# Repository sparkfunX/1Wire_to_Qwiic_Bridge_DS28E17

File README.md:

# Qwiic_1Wire_to_I2C_Bridge_DS28E17
A 1Wire-to- I2C bridge for extending the length of wired I2C networks. For Qwiic Ecosystem.

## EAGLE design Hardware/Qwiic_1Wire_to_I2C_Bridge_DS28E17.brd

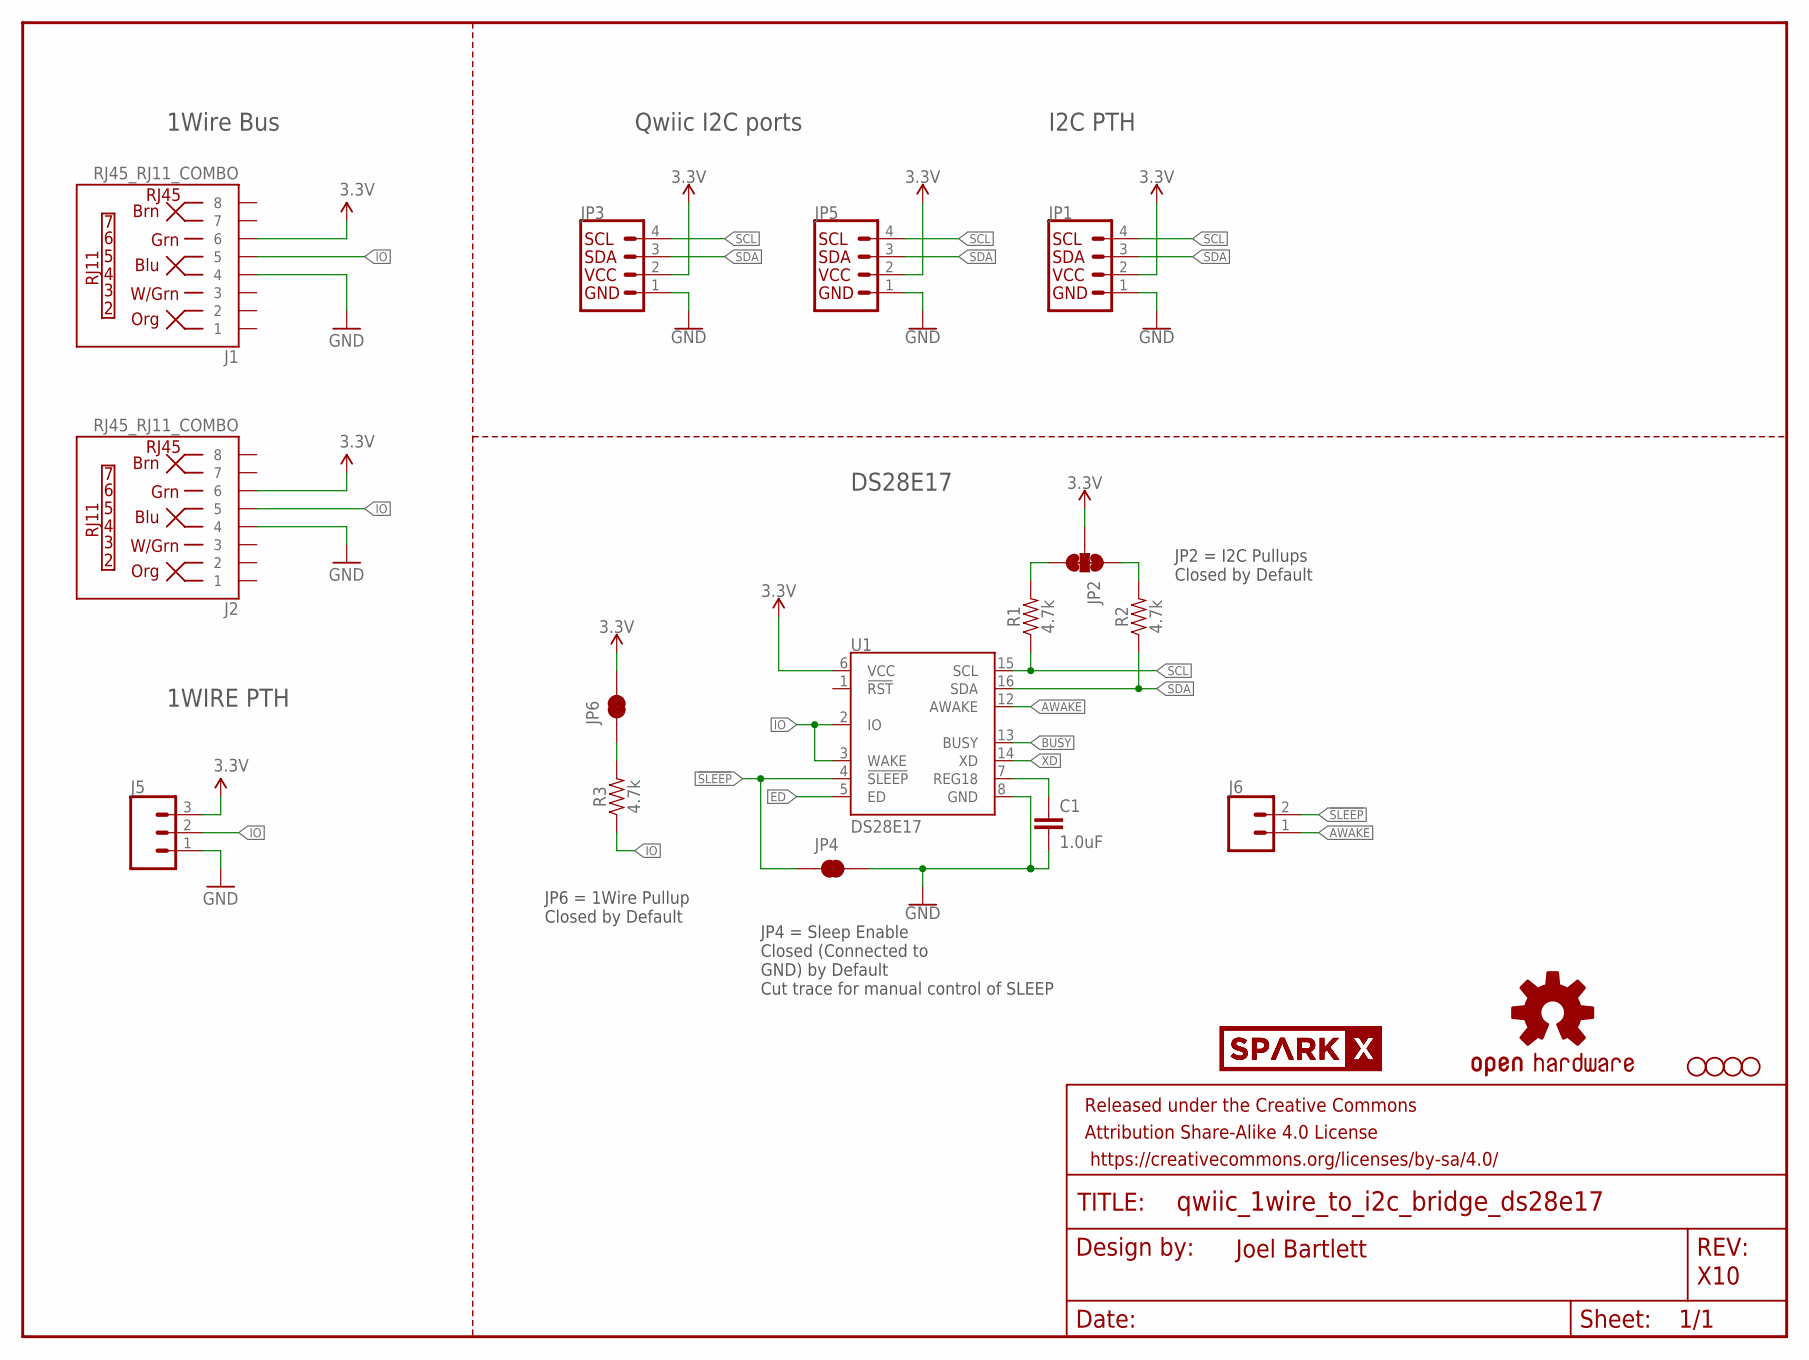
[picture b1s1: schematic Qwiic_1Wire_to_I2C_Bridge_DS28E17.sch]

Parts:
C1: 1.0uF; 0603
FRAME1: FRAME-LETTER; CREATIVE_COMMONS
H1, H2, H3, H4: STAND-OFF
J1, J2: RJ45_RJ11_COMBO
J5: CONN_03; 1X03
J6: CONN_02; 1X02
JP1: I2C_STANDARDSILK; 1X04
JP2: JUMPER-SMT_3_2-NC_TRACE_SILK; SMT-JUMPER_3_2-NC_TRACE_SILK
JP3, JP5: I2C_STANDARDJS-1MM; 1X04_1MM_RA
JP4, JP6: JUMPER-SMT_2_NC_TRACE_SILK; SMT-JUMPER_2_NC_TRACE_SILK
LOGO1: OSHW-LOGOM; OSHW-LOGO-M
R1, R2, R3: 4.7k; 0603
U1: DS28E17; TQFN-16
U$2, U$3: SPARKX-LOGO5; SPARKX-LARGE

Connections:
3.3V: J1.6, J2.6, J5.3, JP1.2 (VCC), JP2.2, JP3.2 (VCC), JP5.2 (VCC), JP6.2, U1.6 (VCC)
!SLEEP: J6.2, JP4.1, U1.4 (!SLEEP)
AWAKE: J6.1, U1.12 (AWAKE)
BUSY: U1.13 (BUSY)
ED: U1.5 (ED)
GND: C1.2, J1.4, J2.4, J5.1, JP1.1 (GND), JP3.1 (GND), JP4.2, JP5.1 (GND), U1.8 (GND)
IO: J1.5, J2.5, J5.2, R3.1, U1.2 (IO), U1.3 (WAKE)
unnamed: C1.1, U1.7 (REG18)
unnamed: JP6.1, R3.2
unnamed: JP2.1, R2.2
unnamed: JP2.3, R1.2
SCL: JP1.4 (SCL), JP3.4 (SCL), JP5.4 (SCL), R1.1, U1.15 (SCL)
SDA: JP1.3 (SDA), JP3.3 (SDA), JP5.3 (SDA), R2.1, U1.16 (SDA)
XD: U1.14 (XD)

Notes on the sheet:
1Wire Bus
Joel Bartlett
Qwiic I2C ports
X10
I2C PTH
DS28E17
1WIRE PTH
JP2 = I2C Pullups Closed by Default
JP6 = 1Wire Pullup Closed by Default
JP4 = Sleep Enable Closed (Connected to GND) by Default Cut trace for manual control of SLEEP

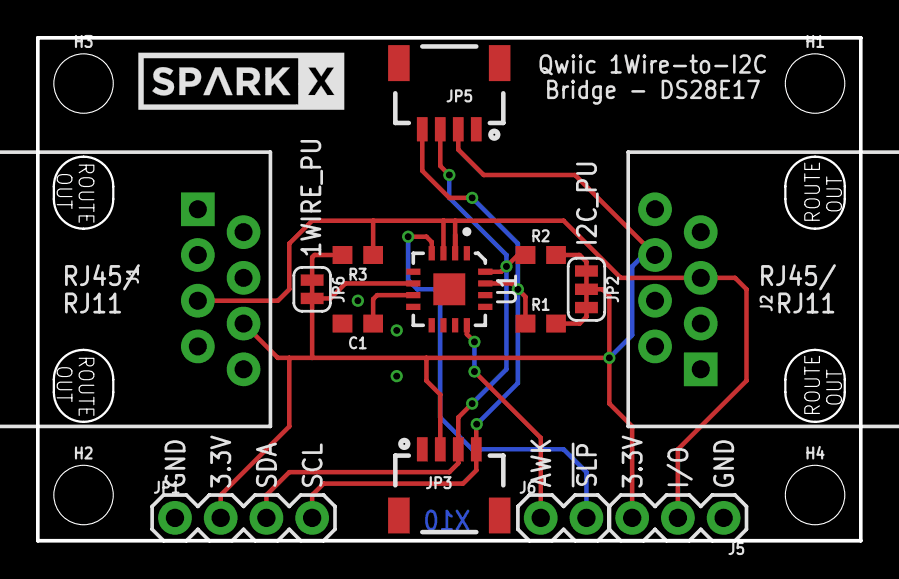
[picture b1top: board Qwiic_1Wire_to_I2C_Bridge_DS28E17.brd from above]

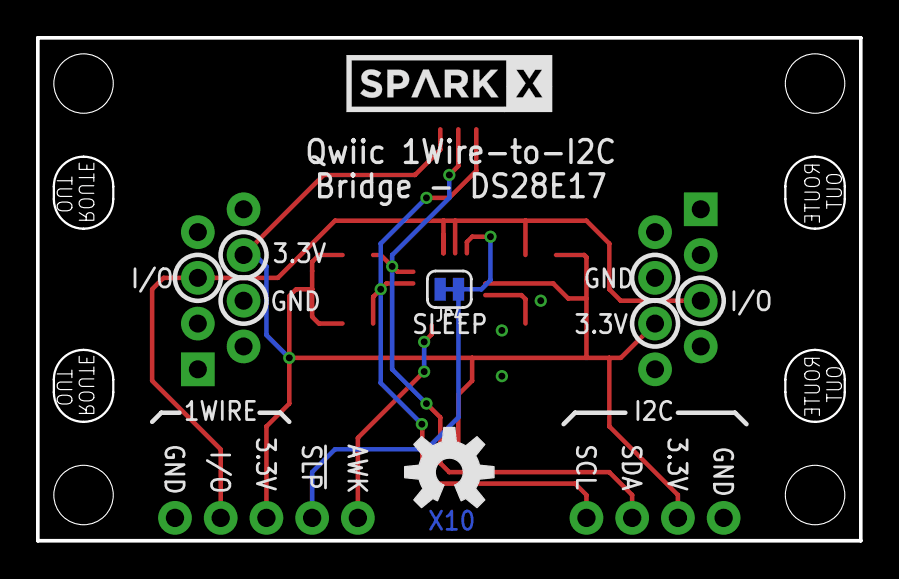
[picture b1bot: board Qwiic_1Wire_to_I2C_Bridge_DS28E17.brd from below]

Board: 2 copper layers, 45.7 x 27.9 mm, 23 parts (3 on the bottom side), 11 nets.

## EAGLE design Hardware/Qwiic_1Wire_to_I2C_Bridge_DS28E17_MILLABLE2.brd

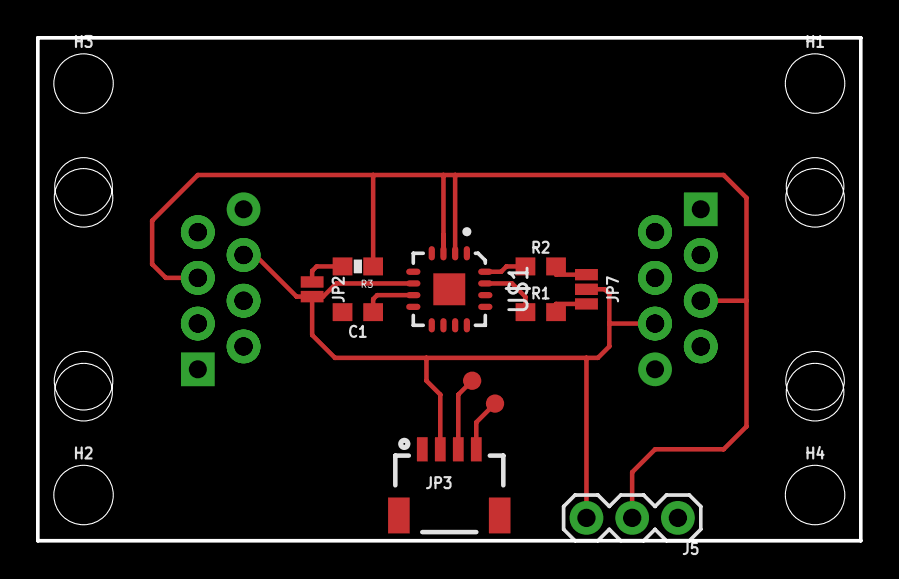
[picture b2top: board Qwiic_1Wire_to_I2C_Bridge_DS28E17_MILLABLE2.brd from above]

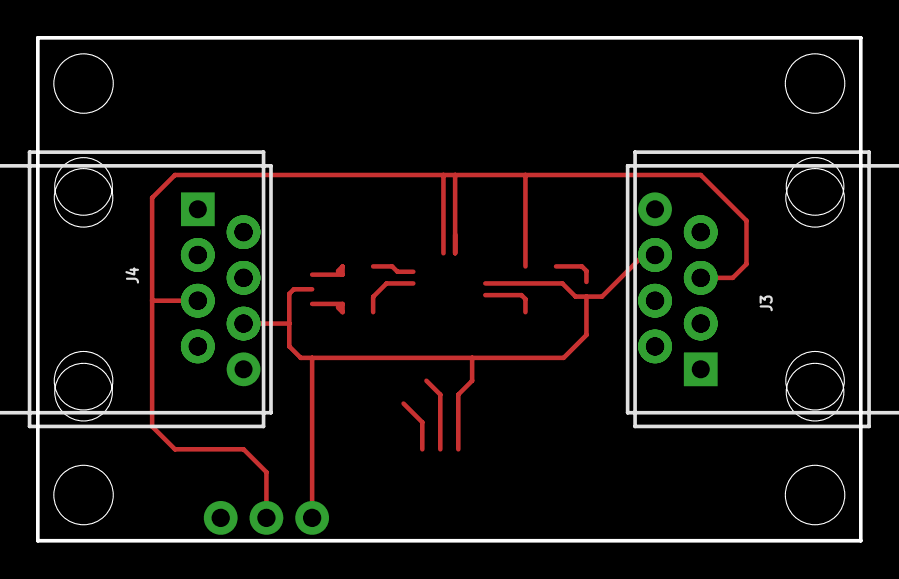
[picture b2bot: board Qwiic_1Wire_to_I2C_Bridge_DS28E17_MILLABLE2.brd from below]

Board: 2 copper layers, 45.7 x 27.9 mm, 20 parts (4 on the bottom side), 11 nets.

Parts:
C1: 1.0uF; 0603
FRAME1: FRAME-LETTER; CREATIVE_COMMONS
H1, H2, H3, H4: STAND-OFF
J1, J2: RJ45; RJ45-8
J3, J4: RJ11; RJ11-6
J5: 1X03
JP2: SMT-JUMPER_2_NO_NO-SILK
JP3: 1X04_1MM_RA
JP7: SMT-JUMPER_3_NO_NO-SILK
R1, R2: 4.7k; 0603
R3: 4.7K; 0603-RES
TP1, TP2: TEST-POINT3X4; PAD.03X.04
U$1: DS28E17; TQFN-16

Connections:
3.3V: J1.6, J2.6, J3.5, J4.5, J5.3, JP2.2, JP3.2, JP7.2, U$1.6
GND: C1.2, J1.4, J2.4, J3.3, J4.3, J5.1, JP3.1, U$1.4, U$1.8
IO: J1.5, J2.5, J3.4, J4.4, J5.2, R3.1, U$1.2, U$1.3
unnamed: C1.1, U$1.7
unnamed: JP2.1, R3.2
unnamed: JP7.1, R2.2
unnamed: JP7.3, R1.2
unnamed: JP3.4, TP1.P$1
unnamed: JP3.3, TP2.P$1
SCL: R1.1, U$1.15
SDA: R2.1, U$1.16

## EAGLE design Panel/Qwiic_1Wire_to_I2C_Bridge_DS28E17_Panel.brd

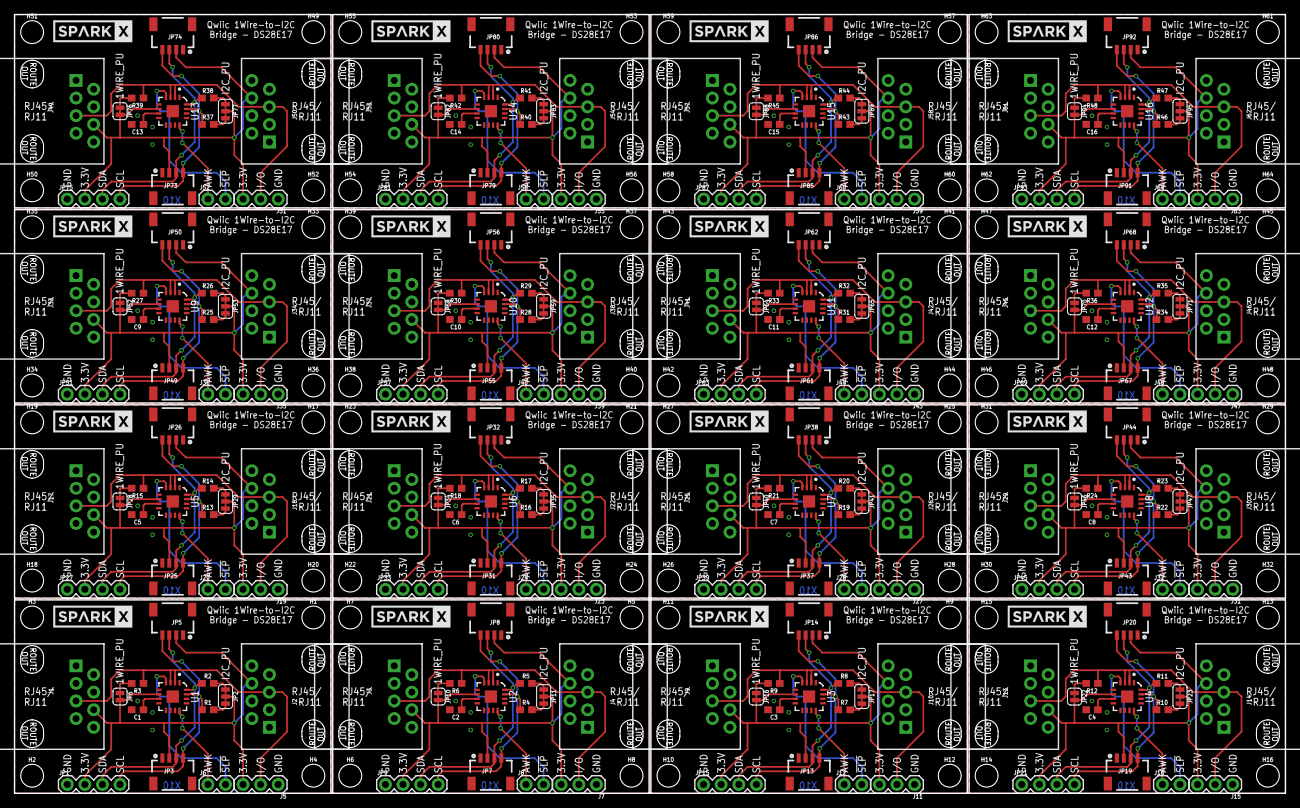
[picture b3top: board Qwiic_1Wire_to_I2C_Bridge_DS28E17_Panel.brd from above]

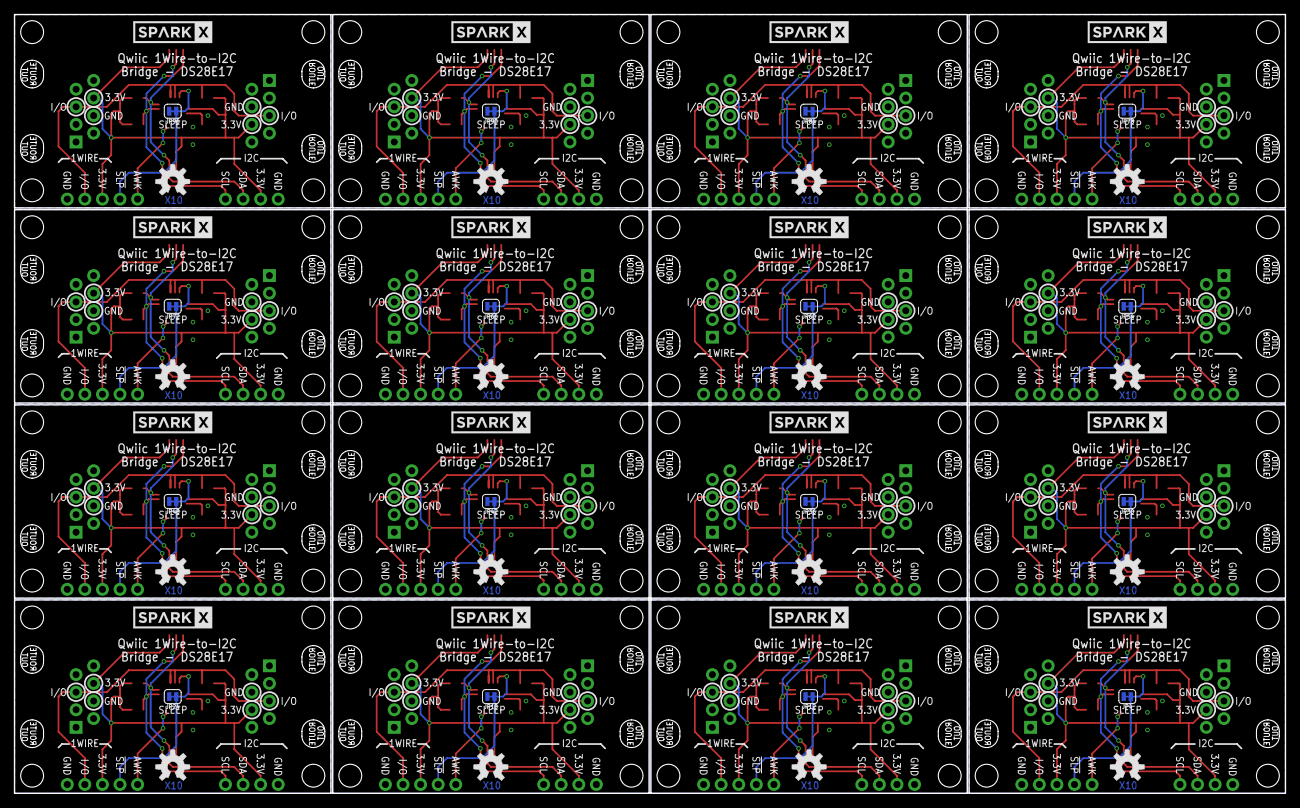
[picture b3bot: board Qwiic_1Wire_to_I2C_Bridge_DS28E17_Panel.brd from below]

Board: 2 copper layers, 183.6 x 112.5 mm, 353 parts (48 on the bottom side), 176 nets.

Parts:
C1, C2, C3, C4, C5, C6, C7, C8, C9, C10, C11, C12, C13, C14, C15, C16: 1.0uF; 0603
FRAME1: FRAME-LETTER; CREATIVE_COMMONS
H1, H2, H3, H4, H5, H6, H7, H8, H9, H10, H11, H12, H13, H14, H15, H16, H17, H18, H19, H20, H21, H22, H23, H24, H25, H26, H27, H28, H29, H30, H31, H32, H33, H34, H35, H36, H37, H38, H39, H40, H41, H42, H43, H44, H45, H46, H47, H48, H49, H50, H51, H52, H53, H54, H55, H56, H57, H58, H59, H60, H61, H62, H63, H64: STAND-OFF
J1, J2, J3, J4, J9, J10, J13, J14, J17, J18, J21, J22, J25, J26, J29, J30, J33, J34, J37, J38, J41, J42, J45, J46, J49, J50, J53, J54, J57, J58, J61, J62: RJ45_RJ11_COMBO
J5, J7, J11, J15, J19, J23, J27, J31, J35, J39, J43, J47, J51, J55, J59, J63: 1X03
J6, J8, J12, J16, J20, J24, J28, J32, J36, J40, J44, J48, J52, J56, J60, J64: 1X02
JP1, JP9, JP15, JP21, JP27, JP33, JP39, JP45, JP51, JP57, JP63, JP69, JP75, JP81, JP87, JP93: 1X04
JP2, JP11, JP17, JP23, JP29, JP35, JP41, JP47, JP53, JP59, JP65, JP71, JP77, JP83, JP89, JP95: SMT-JUMPER_3_2-NC_TRACE_SILK
JP3, JP5, JP7, JP8, JP13, JP14, JP19, JP20, JP25, JP26, JP31, JP32, JP37, JP38, JP43, JP44, JP49, JP50, JP55, JP56, JP61, JP62, JP67, JP68, JP73, JP74, JP79, JP80, JP85, JP86, JP91, JP92: 1X04_1MM_RA
JP4, JP6, JP10, JP12, JP16, JP18, JP22, JP24, JP28, JP30, JP34, JP36, JP40, JP42, JP46, JP48, JP52, JP54, JP58, JP60, JP64, JP66, JP70, JP72, JP76, JP78, JP82, JP84, JP88, JP90, JP94, JP96: SMT-JUMPER_2_NC_TRACE_SILK
LOGO1, LOGO2, LOGO3, LOGO4, LOGO5, LOGO6, LOGO7, LOGO8, LOGO9, LOGO10, LOGO11, LOGO12, LOGO13, LOGO14, LOGO15, LOGO16: OSHW-LOGOM; OSHW-LOGO-M
R1, R2, R3, R4, R5, R6, R7, R8, R9, R10, R11, R12, R13, R14, R15, R16, R17, R18, R19, R20, R21, R22, R23, R24, R25, R26, R27, R28, R29, R30, R31, R32, R33, R34, R35, R36, R37, R38, R39, R40, R41, R42, R43, R44, R45, R46, R47, R48: 4.7k; 0603
U1, U2, U3, U4, U5, U6, U7, U8, U9, U10, U11, U12, U13, U14, U15, U16: DS28E17; TQFN-16
U$1, U$2, U$3, U$4, U$5, U$6, U$7, U$8, U$9, U$10, U$11, U$12, U$13, U$14, U$15, U$16, U$17, U$18, U$19, U$20, U$21, U$22, U$23, U$24, U$25, U$26, U$27, U$28, U$29, U$30, U$31, U$32: SPARKX-LOGO5; SPARKX-LARGE

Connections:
3.3V: J1.6, J2.6, J5.3, JP1.2, JP2.2, JP3.2, JP5.2, JP6.2, U1.6
3.3V1: J3.6, J4.6, J7.3, JP7.2, JP8.2, JP9.2, JP10.2, JP11.2, U2.6
3.3V2: J9.6, J10.6, J11.3, JP13.2, JP14.2, JP15.2, JP16.2, JP17.2, U3.6
3.3V3: J13.6, J14.6, J15.3, JP19.2, JP20.2, JP21.2, JP22.2, JP23.2, U4.6
3.3V4: J17.6, J18.6, J19.3, JP25.2, JP26.2, JP27.2, JP28.2, JP29.2, U5.6
3.3V5: J21.6, J22.6, J23.3, JP31.2, JP32.2, JP33.2, JP34.2, JP35.2, U6.6
3.3V6: J25.6, J26.6, J27.3, JP37.2, JP38.2, JP39.2, JP40.2, JP41.2, U7.6
3.3V7: J29.6, J30.6, J31.3, JP43.2, JP44.2, JP45.2, JP46.2, JP47.2, U8.6
3.3V8: J33.6, J34.6, J35.3, JP49.2, JP50.2, JP51.2, JP52.2, JP53.2, U9.6
3.3V9: J37.6, J38.6, J39.3, JP55.2, JP56.2, JP57.2, JP58.2, JP59.2, U10.6
3.3V10: J41.6, J42.6, J43.3, JP61.2, JP62.2, JP63.2, JP64.2, JP65.2, U11.6
3.3V11: J45.6, J46.6, J47.3, JP67.2, JP68.2, JP69.2, JP70.2, JP71.2, U12.6
3.3V12: J49.6, J50.6, J51.3, JP73.2, JP74.2, JP75.2, JP76.2, JP77.2, U13.6
3.3V13: J53.6, J54.6, J55.3, JP79.2, JP80.2, JP81.2, JP82.2, JP83.2, U14.6
3.3V14: J57.6, J58.6, J59.3, JP85.2, JP86.2, JP87.2, JP88.2, JP89.2, U15.6
3.3V15: J61.6, J62.6, J63.3, JP91.2, JP92.2, JP93.2, JP94.2, JP95.2, U16.6
!SLEEP: J6.2, JP4.1, U1.4
!SLEEP1: J8.2, JP12.1, U2.4
!SLEEP2: J12.2, JP18.1, U3.4
!SLEEP3: J16.2, JP24.1, U4.4
!SLEEP4: J20.2, JP30.1, U5.4
!SLEEP5: J24.2, JP36.1, U6.4
!SLEEP6: J28.2, JP42.1, U7.4
!SLEEP7: J32.2, JP48.1, U8.4
!SLEEP8: J36.2, JP54.1, U9.4
!SLEEP9: J40.2, JP60.1, U10.4
!SLEEP10: J44.2, JP66.1, U11.4
!SLEEP11: J48.2, JP72.1, U12.4
!SLEEP12: J52.2, JP78.1, U13.4
!SLEEP13: J56.2, JP84.1, U14.4
!SLEEP14: J60.2, JP90.1, U15.4
!SLEEP15: J64.2, JP96.1, U16.4
AWAKE: J6.1, U1.12
AWAKE1: J8.1, U2.12
AWAKE2: J12.1, U3.12
AWAKE3: J16.1, U4.12
AWAKE4: J20.1, U5.12
AWAKE5: J24.1, U6.12
AWAKE6: J28.1, U7.12
AWAKE7: J32.1, U8.12
AWAKE8: J36.1, U9.12
AWAKE9: J40.1, U10.12
AWAKE10: J44.1, U11.12
AWAKE11: J48.1, U12.12
AWAKE12: J52.1, U13.12
AWAKE13: J56.1, U14.12
AWAKE14: J60.1, U15.12
AWAKE15: J64.1, U16.12
GND: C1.2, J1.4, J2.4, J5.1, JP1.1, JP3.1, JP4.2, JP5.1, U1.8
GND1: C2.2, J3.4, J4.4, J7.1, JP7.1, JP8.1, JP9.1, JP12.2, U2.8
GND2: C3.2, J9.4, J10.4, J11.1, JP13.1, JP14.1, JP15.1, JP18.2, U3.8
GND3: C4.2, J13.4, J14.4, J15.1, JP19.1, JP20.1, JP21.1, JP24.2, U4.8
GND4: C5.2, J17.4, J18.4, J19.1, JP25.1, JP26.1, JP27.1, JP30.2, U5.8
GND5: C6.2, J21.4, J22.4, J23.1, JP31.1, JP32.1, JP33.1, JP36.2, U6.8
GND6: C7.2, J25.4, J26.4, J27.1, JP37.1, JP38.1, JP39.1, JP42.2, U7.8
GND7: C8.2, J29.4, J30.4, J31.1, JP43.1, JP44.1, JP45.1, JP48.2, U8.8
GND8: C9.2, J33.4, J34.4, J35.1, JP49.1, JP50.1, JP51.1, JP54.2, U9.8
GND9: C10.2, J37.4, J38.4, J39.1, JP55.1, JP56.1, JP57.1, JP60.2, U10.8
GND10: C11.2, J41.4, J42.4, J43.1, JP61.1, JP62.1, JP63.1, JP66.2, U11.8
GND11: C12.2, J45.4, J46.4, J47.1, JP67.1, JP68.1, JP69.1, JP72.2, U12.8
GND12: C13.2, J49.4, J50.4, J51.1, JP73.1, JP74.1, JP75.1, JP78.2, U13.8
GND13: C14.2, J53.4, J54.4, J55.1, JP79.1, JP80.1, JP81.1, JP84.2, U14.8
GND14: C15.2, J57.4, J58.4, J59.1, JP85.1, JP86.1, JP87.1, JP90.2, U15.8
GND15: C16.2, J61.4, J62.4, J63.1, JP91.1, JP92.1, JP93.1, JP96.2, U16.8
IO: J1.5, J2.5, J5.2, R3.1, U1.2, U1.3
IO1: J3.5, J4.5, J7.2, R6.1, U2.2, U2.3
IO2: J9.5, J10.5, J11.2, R9.1, U3.2, U3.3
IO3: J13.5, J14.5, J15.2, R12.1, U4.2, U4.3
IO4: J17.5, J18.5, J19.2, R15.1, U5.2, U5.3
IO5: J21.5, J22.5, J23.2, R18.1, U6.2, U6.3
IO6: J25.5, J26.5, J27.2, R21.1, U7.2, U7.3
IO7: J29.5, J30.5, J31.2, R24.1, U8.2, U8.3
IO8: J33.5, J34.5, J35.2, R27.1, U9.2, U9.3
IO9: J37.5, J38.5, J39.2, R30.1, U10.2, U10.3
IO10: J41.5, J42.5, J43.2, R33.1, U11.2, U11.3
IO11: J45.5, J46.5, J47.2, R36.1, U12.2, U12.3
IO12: J49.5, J50.5, J51.2, R39.1, U13.2, U13.3
IO13: J53.5, J54.5, J55.2, R42.1, U14.2, U14.3
IO14: J57.5, J58.5, J59.2, R45.1, U15.2, U15.3
IO15: J61.5, J62.5, J63.2, R48.1, U16.2, U16.3
unnamed: C1.1, U1.7
unnamed: JP6.1, R3.2
unnamed: JP2.1, R2.2
unnamed: JP2.3, R1.2
unnamed: C2.1, U2.7
unnamed: JP10.1, R6.2
unnamed: JP11.1, R5.2
unnamed: JP11.3, R4.2
unnamed: C3.1, U3.7
unnamed: JP16.1, R9.2
unnamed: JP17.1, R8.2
unnamed: JP17.3, R7.2
unnamed: C4.1, U4.7
unnamed: JP22.1, R12.2
unnamed: JP23.1, R11.2
unnamed: JP23.3, R10.2
unnamed: C5.1, U5.7
unnamed: JP28.1, R15.2
unnamed: JP29.1, R14.2
unnamed: JP29.3, R13.2
unnamed: C6.1, U6.7
unnamed: JP34.1, R18.2
unnamed: JP35.1, R17.2
unnamed: JP35.3, R16.2
unnamed: C7.1, U7.7
unnamed: JP40.1, R21.2
unnamed: JP41.1, R20.2
unnamed: JP41.3, R19.2
unnamed: C8.1, U8.7
unnamed: JP46.1, R24.2
unnamed: JP47.1, R23.2
unnamed: JP47.3, R22.2
unnamed: C9.1, U9.7
unnamed: JP52.1, R27.2
unnamed: JP53.1, R26.2
unnamed: JP53.3, R25.2
unnamed: C10.1, U10.7
unnamed: JP58.1, R30.2
unnamed: JP59.1, R29.2
unnamed: JP59.3, R28.2
unnamed: C11.1, U11.7
unnamed: JP64.1, R33.2
unnamed: JP65.1, R32.2
unnamed: JP65.3, R31.2
unnamed: C12.1, U12.7
unnamed: JP70.1, R36.2
unnamed: JP71.1, R35.2
unnamed: JP71.3, R34.2
unnamed: C13.1, U13.7
unnamed: JP76.1, R39.2
unnamed: JP77.1, R38.2
unnamed: JP77.3, R37.2
unnamed: C14.1, U14.7
unnamed: JP82.1, R42.2
unnamed: JP83.1, R41.2
unnamed: JP83.3, R40.2
unnamed: C15.1, U15.7
unnamed: JP88.1, R45.2
unnamed: JP89.1, R44.2
unnamed: JP89.3, R43.2
unnamed: C16.1, U16.7
unnamed: JP94.1, R48.2
unnamed: JP95.1, R47.2
unnamed: JP95.3, R46.2
SCL: JP1.4, JP3.4, JP5.4, R1.1, U1.15
SCL1: JP7.4, JP8.4, JP9.4, R4.1, U2.15
SCL2: JP13.4, JP14.4, JP15.4, R7.1, U3.15
SCL3: JP19.4, JP20.4, JP21.4, R10.1, U4.15
SCL4: JP25.4, JP26.4, JP27.4, R13.1, U5.15
SCL5: JP31.4, JP32.4, JP33.4, R16.1, U6.15
SCL6: JP37.4, JP38.4, JP39.4, R19.1, U7.15
SCL7: JP43.4, JP44.4, JP45.4, R22.1, U8.15
SCL8: JP49.4, JP50.4, JP51.4, R25.1, U9.15
SCL9: JP55.4, JP56.4, JP57.4, R28.1, U10.15
SCL10: JP61.4, JP62.4, JP63.4, R31.1, U11.15
SCL11: JP67.4, JP68.4, JP69.4, R34.1, U12.15
SCL12: JP73.4, JP74.4, JP75.4, R37.1, U13.15
SCL13: JP79.4, JP80.4, JP81.4, R40.1, U14.15
SCL14: JP85.4, JP86.4, JP87.4, R43.1, U15.15
SCL15: JP91.4, JP92.4, JP93.4, R46.1, U16.15
SDA: JP1.3, JP3.3, JP5.3, R2.1, U1.16
SDA1: JP7.3, JP8.3, JP9.3, R5.1, U2.16
SDA2: JP13.3, JP14.3, JP15.3, R8.1, U3.16
SDA3: JP19.3, JP20.3, JP21.3, R11.1, U4.16
SDA4: JP25.3, JP26.3, JP27.3, R14.1, U5.16
SDA5: JP31.3, JP32.3, JP33.3, R17.1, U6.16
SDA6: JP37.3, JP38.3, JP39.3, R20.1, U7.16
SDA7: JP43.3, JP44.3, JP45.3, R23.1, U8.16
SDA8: JP49.3, JP50.3, JP51.3, R26.1, U9.16
SDA9: JP55.3, JP56.3, JP57.3, R29.1, U10.16
SDA10: JP61.3, JP62.3, JP63.3, R32.1, U11.16
SDA11: JP67.3, JP68.3, JP69.3, R35.1, U12.16
SDA12: JP73.3, JP74.3, JP75.3, R38.1, U13.16
SDA13: JP79.3, JP80.3, JP81.3, R41.1, U14.16
SDA14: JP85.3, JP86.3, JP87.3, R44.1, U15.16
SDA15: JP91.3, JP92.3, JP93.3, R47.1, U16.16

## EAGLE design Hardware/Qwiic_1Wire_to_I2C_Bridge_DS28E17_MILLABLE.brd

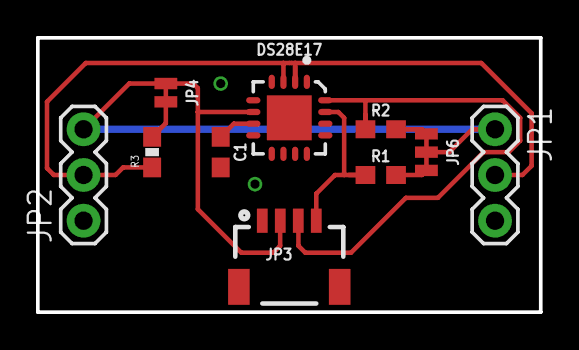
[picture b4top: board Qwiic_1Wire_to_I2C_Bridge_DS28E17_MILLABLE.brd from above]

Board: 2 copper layers, 27.9 x 15.2 mm, 11 parts (0 on the bottom side), 9 nets.

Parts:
C1: 1.0uF; 0603
FRAME1: FRAME-LETTER; CREATIVE_COMMONS
JP1: 1Wire_OUT; 1X03
JP2: 1Wire_IN; 1X03
JP3: 1X04_1MM_RA
JP4: SMT-JUMPER_2_NC_TRACE_NO-SILK
JP6: SMT-JUMPER_3_2-NC_TRACE_NO-SILK
R1, R2: 4.7k; 0603
R3: 4.7K; 0603-RES
U$2: DS28E17; TQFN-16_4X4

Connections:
3.3V: JP1.1, JP2.3, JP3.2, JP4.2, JP6.2, U$2.6
GND: C1.2, JP1.3, JP2.1, JP3.1, U$2.4, U$2.8
IO: JP1.2, JP2.2, R3.1, U$2.2, U$2.3
unnamed: C1.1, U$2.7
unnamed: JP4.1, R3.2
unnamed: JP6.1, R2.2
unnamed: JP6.3, R1.2
SCL: JP3.4, R1.1, U$2.15
SDA: JP3.3, R2.1, U$2.16

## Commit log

2017-04-03 update gitignore
2017-04-05 Routed more on production layout
2017-04-06 MIllable version 2
2017-04-08 Update to board
2017-04-11 Added RJ45/RJ11 footprint. CAM new panel gerbers
2017-04-20 Adding Arduino sketch examples

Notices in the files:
parts and their libraries:
SparkFun-Aesthetics: Licensing: CC v3.0 Share-Alike You are welcome to use this library for commercial purposes.
SparkFun-Aesthetics: Released under the Creative Commons Attribution Share-Alike 4.0 License
SparkFun-Aesthetics: https://creativecommons.org/licenses/by-sa/4.0
